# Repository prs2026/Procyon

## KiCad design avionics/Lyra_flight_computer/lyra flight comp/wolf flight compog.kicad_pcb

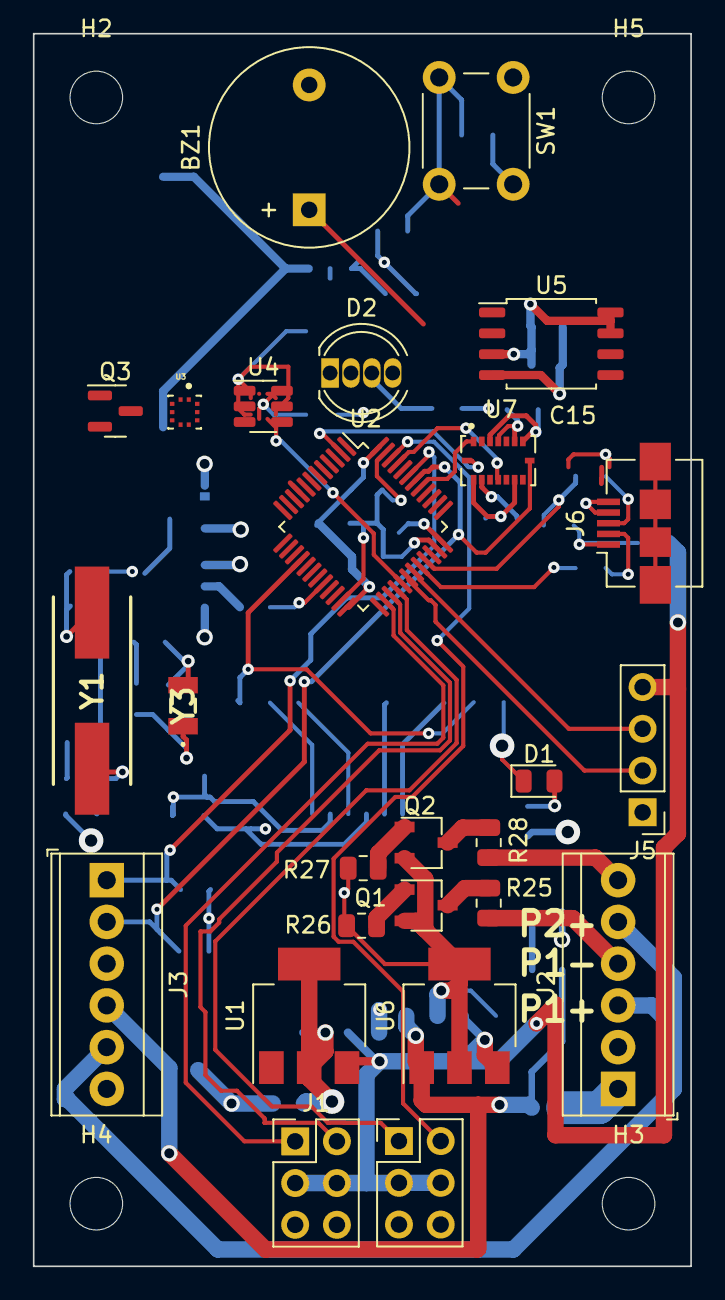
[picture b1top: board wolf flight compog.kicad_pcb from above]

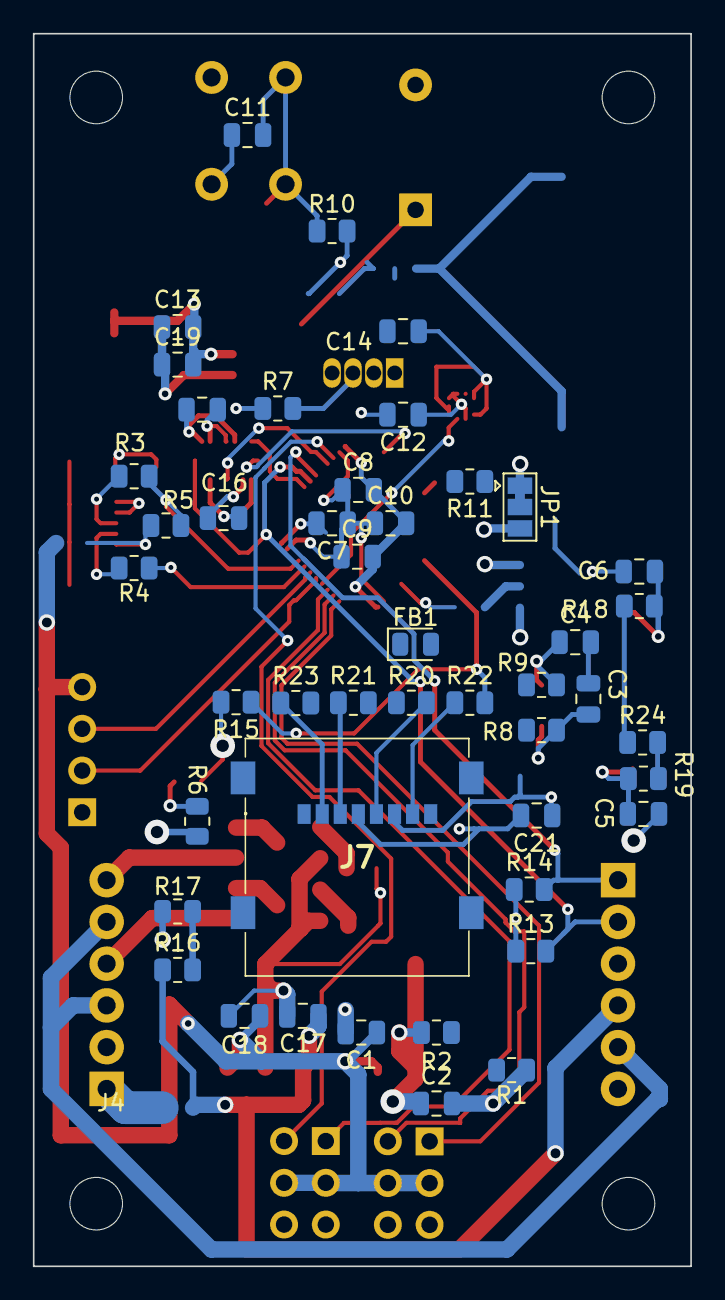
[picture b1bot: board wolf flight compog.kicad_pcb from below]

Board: 4 copper layers, 40.0 x 75.0 mm, 76 parts (46 on the bottom side), 58 nets.

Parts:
BZ1: Buzzer; Buzzer_12x9.5RM7.6
C1, C12, C13, C14, C15, C16, C17: 0.1uf; C_0805_2012Metric
C2, C18, C19, C21: 1uf; C_0805_2012Metric
C3, C4, C5, C6: 20pf; C_0805_2012Metric
C7: 10uf; C_0805_2012Metric
C8, C9, C10, C11: 100nf; C_0805_2012Metric
D1: LED; LED_0805_2012Metric
D2: LED_RBKG; LED_D5.0mm-4_RGB
FB1: FerriteBead; D_0805_2012Metric
H2, H3, H4, H5: MountingHole; MountingHole_3.2mm_M3
J1, J4: Conn_02x03_Top_Bottom; PinHeader_2x03_P2.54mm_Vertical
J2, J3: Screw_Terminal_01x06; TerminalBlock_TE_282834-6_1x06_P2.54mm_Horizontal
J5: Conn_01x04; PinHeader_1x04_P2.54mm_Vertical
J6: USB_B_Micro; USB_Micro-B_Amphenol_10104110_Horizontal
J7: MEM2067-02-180-00-A; MEM20670218000A
JP1: SolderJumper_3_Bridged12; SolderJumper-3_P1.3mm_Bridged12_Pad1.0x1.5mm
Q1, Q2: Q_NMOS_GSD; TSOT-23
Q3: AO3401A; SOT-23
R1: 390; R_0805_2012Metric
R2: 240; R_0805_2012Metric
R3, R4: 20; R_0805_2012Metric
R5: 1k5; R_0805_2012Metric
R6, R7, R26, R27: 470; R_0805_2012Metric
R8, R9, R18, R19: 0; R_0805_2012Metric
R10, R13, R14, R16, R17: 10k; R_0805_2012Metric
R11: 100K; R_0805_2012Metric
R15: 100k; R_0805_2012Metric
R20, R21, R22, R23: 3.3k; R_0805_2012Metric
R24: 1M; R_0805_2012Metric
R25, R28: 10; R_0805_2012Metric
SW1: SW_MEC_5E; SW_PUSH_6mm_H5mm
U1: LM317_SOT-223; SOT-223-3_TabPin2
U2: STM32F103C8Tx; LQFP-48_7x7mm_P0.5mm
U3: BMP390L; XDCR_BMP390L
U4: USBLC6-2SC6; SOT-23-6
U5: W25Q32JVSS; SOIC-8_5.23x5.23mm_P1.27mm
U6: LM7805_TO220; SOT-223-3_TabPin2
U7: BMI088; PQFN50P450X300X100-16N
Y1: ABLS-8.000MHZ-20-B-3-H-T; ABLS8000MHz20B3HT
Y3: SC32S-7PF20PPM; SC32S7PF20PPM

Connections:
+3V3: C2.1, C7.2, C8.2, C9.2, C10.2, C12.1, C13.2, C14.1, C15.1, C16.1, C19.2, C21.2, J7.P4 (VDD), JP1.3 (B), R2.1, R5.1, R6.2, R10.2, R13.1, R14.1, U1.2 (VO), U2.1 (VBAT), U2.24 (VDD), U2.36 (VDD), U2.48 (VDD), U3.1 (VDDIO), U3.6 (~CS), U3.10 (VDD), U5.3 (IO2), U5.7 (IO3), U5.8 (VCC), U7.3 (VDD), U7.7 (PS), U7.11 (VDDIO), U7.14 (CSB1)
+5V: C1.1, C18.1, J1.3, J1.4, J4.3, J4.4, J5.4, U1.3 (VI), U6.3 (VO)
+BATT: J2.1, J3.4, Q3.3 (D), R16.1
ACCEL INT1: U2.2 (PC13), U7.16 (INT1)
ACCEL INT2: U2.41 (PB5), U7.1 (INT2)
ARM-: J2.3, J2.5, J3.5
BARO INT: U2.29 (PA8), U3.7 (INT/DNC)
BATT SENSE: R16.2, R17.1
BOOT0: R11.2, U2.44 (BOOT0)
BUZZER: BZ1.1 (-), U2.18 (PB0)
CS SD: R23.2, U2.10 (PA0)
FLASH CS: U2.14 (PA4), U5.1 (~CS)
GND: BZ1.2 (+), C1.2, C2.2, C5.1, C6.2, C7.1, C8.1, C9.1, C10.1, C11.1, C12.2, C13.1, C14.2, C15.2, C16.2, C17.2, C18.2, C19.1, C21.1, D1.1 (K), J1.5, J1.6, J2.2, J3.3, J4.5, J4.6, J5.1, J6.4 (ID), J6.5 (GND), J7.P6 (VSS), JP1.1 (A), Q1.2 (S), Q2.2 (S), Q3.1 (G), R1.2, R7.1, R15.2, R17.2, R26.1, R27.1, SW1.1, U2.8 (VSSA), U2.23 (VSS), U2.35 (VSS), U2.47 (VSS), U3.3 (VSS/GND), U3.5 (SDO/DNC/SA0), U3.8 (VSS/GND__1), U3.9 (VSS/GND__2), U5.4 (GND), U6.2 (GND), U7.4 (GNDA), U7.6 (GNDIO), U7.10 (SDO2), U7.15 (SDO1)
GYRO INT3: U2.45 (PB8), U7.12 (INT3)
GYRO INT4: U2.25 (PB12), U7.13 (INT4)
LED BLUE: D2.4 (GA), U2.12 (PA2)
LED GREEN: D2.2 (BA), U2.13 (PA3)
LED RED: D2.1 (RA), U2.11 (PA1)
MISO: R15.1, R22.2, U2.16 (PA6), U5.2 (DO(IO1))
MOSI: R21.2, U2.17 (PA7), U5.5 (DI(IO0))
unnamed: C3.1, C4.2
unnamed: C3.2, R8.1, Y3.1
unnamed: C5.2, R19.1, Y1.2
unnamed: C6.1, R18.1, Y1.1
unnamed: D1.2 (A), R6.1
unnamed: D2.3 (K), R7.2
unnamed: J6.3 (D+), R3.2
unnamed: J6.2 (D-), R4.1
unnamed: J7.P2 (CD/DAT3), R23.1
unnamed: J7.P5 (CLK), R20.2
unnamed: J7.P3 (CMD), R21.1
unnamed: J7.P7 (DAT0), R22.1
unnamed: JP1.2 (C), R11.1
unnamed: Q1.3 (D), R25.2
unnamed: Q2.3 (D), R28.2
unnamed: C17.1, Q3.2 (S), U6.1 (VI)
unnamed: R1.1, R2.2, U1.1 (ADJ)
unnamed: C4.1, R9.1, Y3.2 (CRYSTAL_2)
OSCIN: R19.2, R24.2, U2.5 (PD0)
OSCIN2: R8.2, U2.3 (PC14)
OSCOUT: R18.2, R24.1, U2.6 (PD1)
OSCOUT2: R9.2, U2.4 (PC15)
P1-: J2.4, R25.1
P1EN: Q1.1 (G), R26.2
P2-: J2.6, R28.1
P2EN: Q2.1 (G), R27.2
RESET: C11.2, R10.1, SW1.2, U2.7 (NRST)
SCK: R20.1, U2.15 (PA5), U5.6 (CLK)
SCL: J3.2, R13.2, U2.42 (PB6), U3.2 (SCK/SCL), U7.8 (SCL/SCK)
SDA: J3.1, R14.2, U2.43 (PB7), U3.4 (SDI/SDO/SDA), U7.9 (SDA/SDI)
SERVO1: J1.1, U2.26 (PB13)
SERVO2: J1.2, U2.27 (PB14)
SERVO3: J4.1, U2.28 (PB15)
SERVO4: J4.2, U2.46 (PB9)
USART1 RX: J5.3, U2.31 (PA10)
USART1 TX: J5.2, U2.30 (PA9)
USB D+: R3.1, R5.2, U2.33 (PA12)
USB D-: R4.2, U2.32 (PA11)

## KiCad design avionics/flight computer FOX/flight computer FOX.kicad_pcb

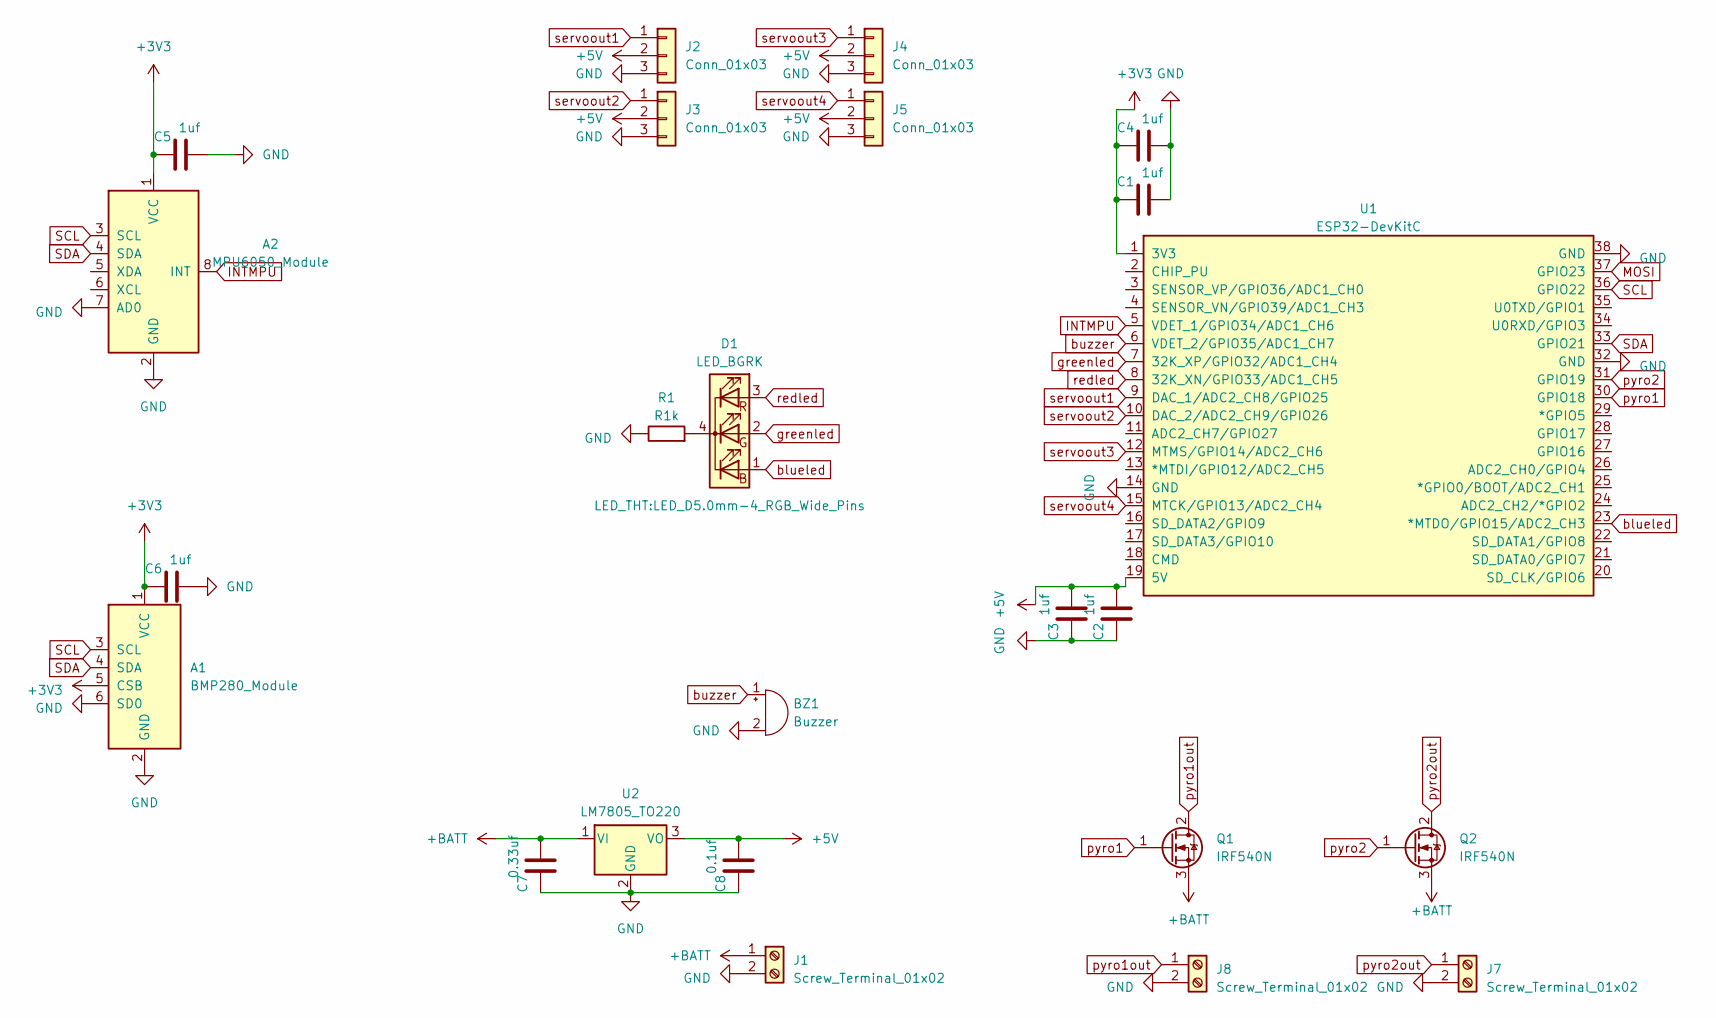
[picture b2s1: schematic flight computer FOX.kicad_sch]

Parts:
A1: BMP280_Module
A2: MPU6050_Module
BZ1: Buzzer; Buzzer_12x9.5RM7.6
C1, C2, C3, C4, C5, C6: 1uf; C_0805_2012Metric_Pad1.18x1.45mm_HandSolder
C7: 0.33uf; C_0805_2012Metric_Pad1.18x1.45mm_HandSolder
C8: 0.1uf; C_0805_2012Metric_Pad1.18x1.45mm_HandSolder
D1: LED_BGRK; LED_D5.0mm-4_RGB_Wide_Pins
J1, J7, J8: Screw_Terminal_01x02; TerminalBlock_bornier-2_P5.08mm
J2, J3, J4, J5: Conn_01x03; PinHeader_1x03_P2.54mm_Vertical
Q1, Q2: IRF540N; TO-220-3_Vertical
R1: R1k; R_0805_2012Metric_Pad1.20x1.40mm_HandSolder
U1: ESP32-DevKitC
U2: LM7805_TO220; TO-220-3_Vertical

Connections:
+3V3: A1.1 (VCC), A1.5 (CSB), A2.1 (VCC), C1.1, C4.1, C5.1, C6.1, U1.1 (3V3)
+5V: C2.2, C3.2, C8.2, J2.2, J3.2, J4.2, J5.2, U1.19 (5V), U2.3 (VO)
+BATT: C7.2, J1.1, Q1.3 (S), Q2.3 (S), U2.1 (VI)
GND: A1.2 (GND), A1.6 (SD0), A2.2 (GND), A2.7 (AD0), BZ1.2 (+), C1.2, C2.1, C3.1, C4.2, C5.2, C6.2, C7.1, C8.1, J1.2, J2.3, J3.3, J4.3, J5.3, J7.2, J8.2, R1.1, U1.14 (GND), U1.32 (GND), U1.38 (GND), U2.2 (GND)
INTMPU: A2.8 (INT), U1.5 (VDET_1/GPIO34/ADC1_CH6)
MOSI: U1.37 (GPIO23)
unnamed: D1.4 (K), R1.2
SCL: A1.3 (SCL), A2.3 (SCL), U1.36 (GPIO22)
SDA: A1.4 (SDA), A2.4 (SDA), U1.33 (GPIO21)
blueled: D1.1 (BA), U1.23 (*MTDO/GPIO15/ADC2_CH3)
buzzer: BZ1.1 (-), U1.6 (VDET_2/GPIO35/ADC1_CH7)
greenled: D1.2 (GA), U1.7 (32K_XP/GPIO32/ADC1_CH4)
pyro1: Q1.1 (G), U1.30 (GPIO18)
pyro1out: J8.1, Q1.2 (D)
pyro2: Q2.1 (G), U1.31 (GPIO19)
pyro2out: J7.1, Q2.2 (D)
redled: D1.3 (RA), U1.8 (32K_XN/GPIO33/ADC1_CH5)
servoout1: J2.1, U1.9 (DAC_1/ADC2_CH8/GPIO25)
servoout2: J3.1, U1.10 (DAC_2/ADC2_CH9/GPIO26)
servoout3: J4.1, U1.12 (MTMS/GPIO14/ADC2_CH6)
servoout4: J5.1, U1.15 (MTCK/GPIO13/ADC2_CH4)

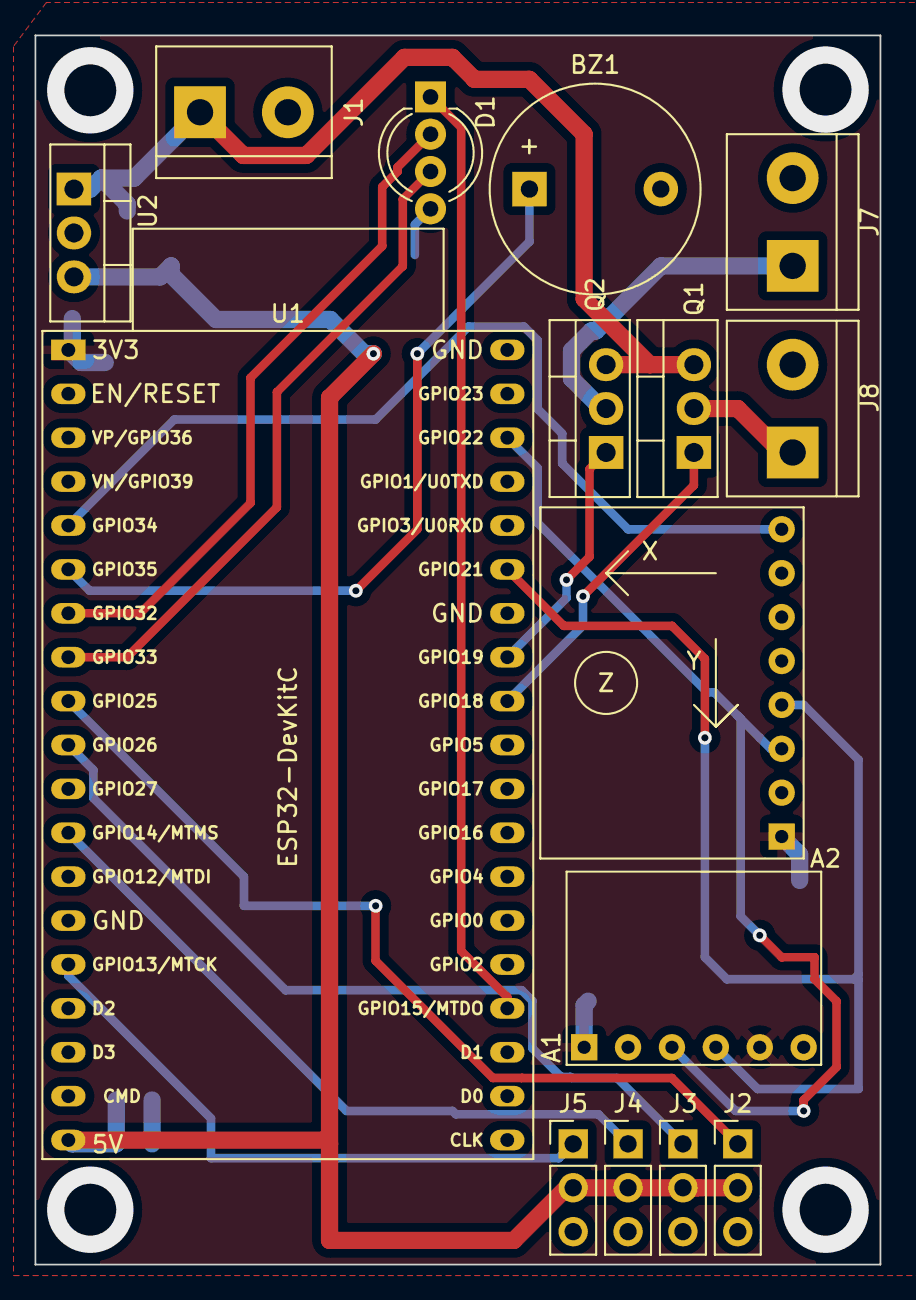
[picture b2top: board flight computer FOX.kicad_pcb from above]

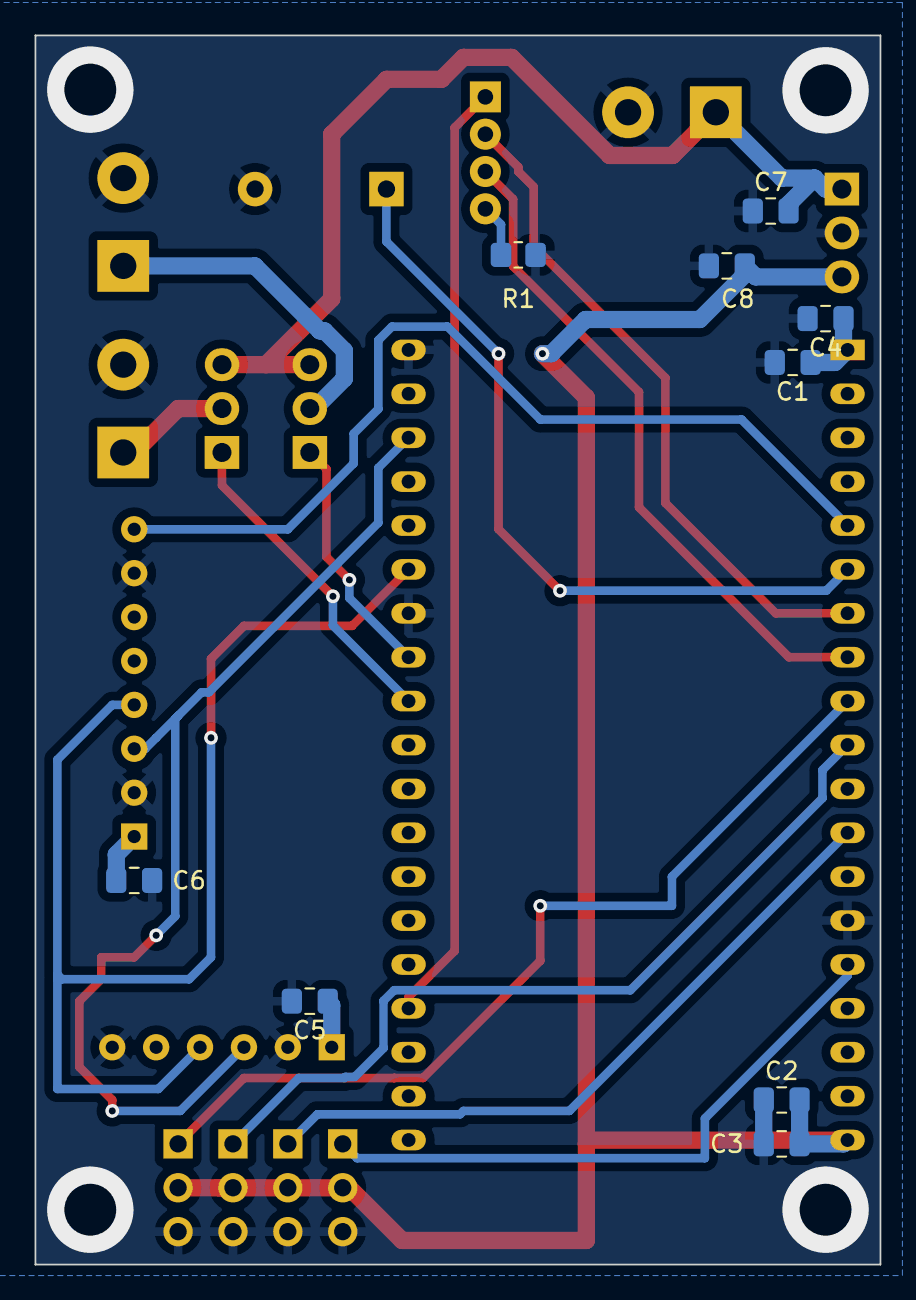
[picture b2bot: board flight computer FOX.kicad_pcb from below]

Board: 2 copper layers, 48.9 x 71.1 mm, 24 parts (9 on the bottom side), 20 nets.

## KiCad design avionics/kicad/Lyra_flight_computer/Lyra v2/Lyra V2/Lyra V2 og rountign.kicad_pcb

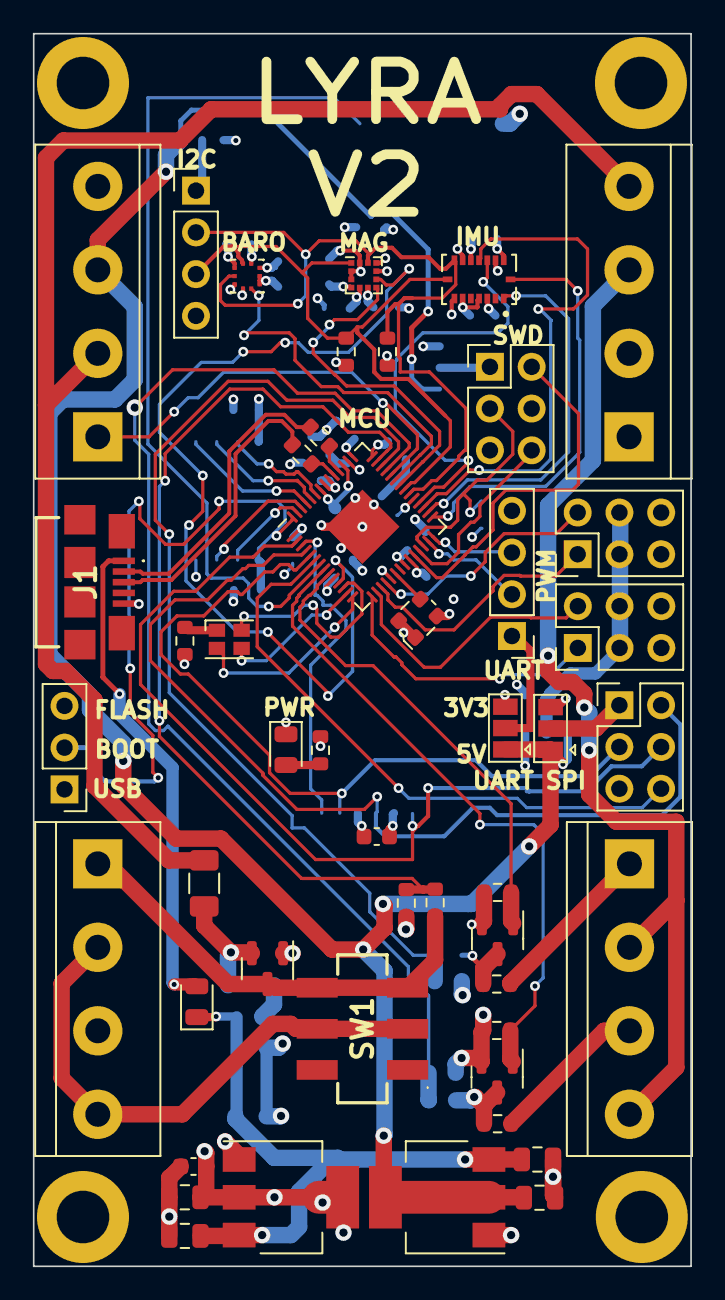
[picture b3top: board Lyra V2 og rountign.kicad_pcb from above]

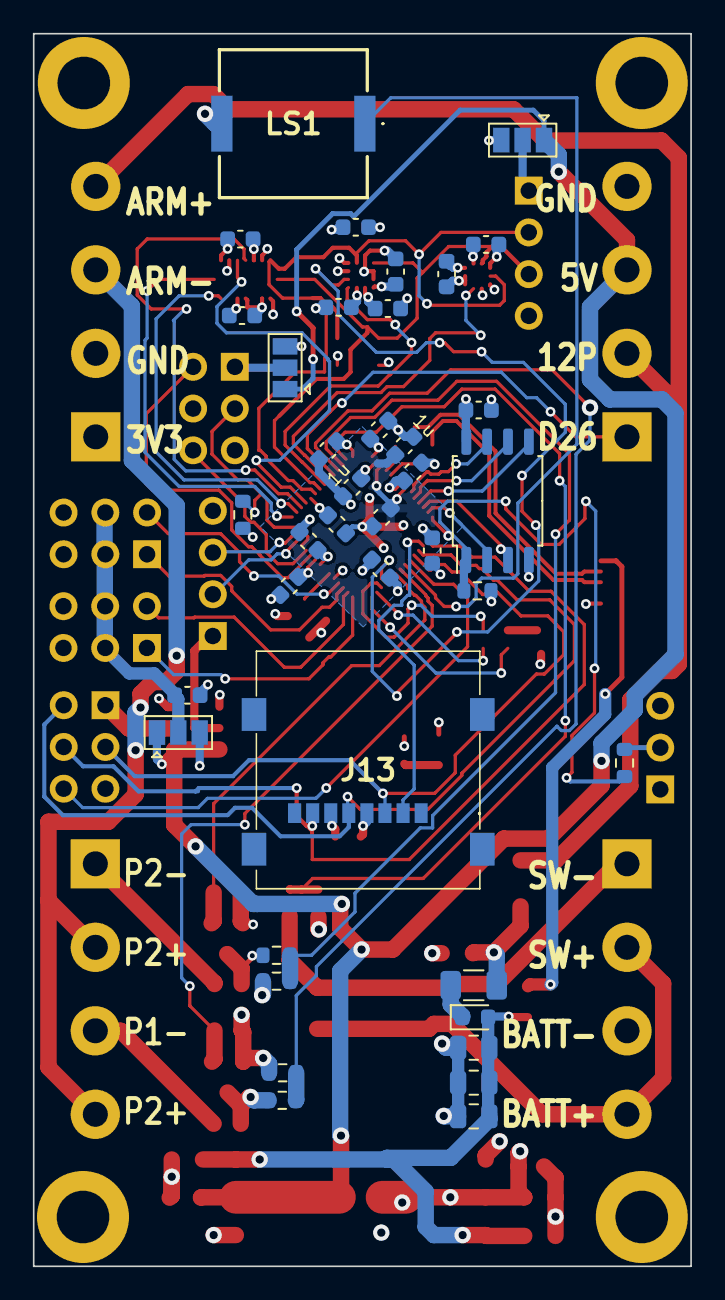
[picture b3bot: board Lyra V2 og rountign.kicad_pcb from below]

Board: 4 copper layers, 40.0 x 75.0 mm, 90 parts (39 on the bottom side), 69 nets.

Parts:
C1, C4, C5, C6: 10u; C_0805_2012Metric
C2, C8: 22u; C_0805_2012Metric
C3, C9, C10, C14, C20, C21: 1u; C_0603_1608Metric
C7: 1u; C_0805_2012Metric
C11, C12, C13, C15, C16, C17, C18, C19, C22, C23, C24, C25, C27, C29, C30: 100n; C_0603_1608Metric
C26, C28: 100nf; C_0603_1608Metric
D1: D_Small; D_0805_2012Metric
D2: LED; LED_0805_2012Metric
D3: CLV1L-FKB; LED_Cree-PLCC4_2x2mm_CW
F1: 2a; Fuse_1206_3216Metric
F2: 200ma; Fuse_1206_3216Metric
FB1: FerriteBead_Small; D_0603_1608Metric
H1, H2, H3, H4: MountingHole_Pad; MountingHole_3.2mm_M3_DIN965_Pad
J1: USB_B_Micro; 101181920001LF
J2, J3, J5, J6: Screw_Terminal_01x04; TerminalBlock_bornier-4_P5.08mm
J4, J7, J8, J9: Conn_02x03_Odd_Even; PinHeader_2x03_P2.54mm_Vertical
J10, J11: Conn_01x04; PinHeader_1x04_P2.54mm_Vertical
J12: Conn_01x03; PinHeader_1x03_P2.54mm_Vertical
J13: MEM2067-02-180-00-A; MEM20670218000A
JP1, JP2, JP3, JP4, JP5: SolderJumper_3_Open; SolderJumper-3_P1.3mm_Open_Pad1.0x1.5mm
LS1: PKMCS0909E4000-R1; PKMCS0909E4000R1
Q1: AO3401A; SOT-23
Q2, Q3: BSS138; SOT-23
R1, R13: 1k; R_0603_1608Metric
R2, R3: 470R; R_0603_1608Metric
R4, R5: 10R; R_0603_1608Metric
R6, R8, R10: 20k; R_0603_1608Metric
R7, R9, R11: 6k; R_0603_1608Metric
R12: R_Small; R_0603_1608Metric
R14: DNF; R_0603_1608Metric
R15, R16: 27R; R_0603_1608Metric
R17, R18: 2k2; R_0603_1608Metric
R19: 10k; R_0603_1608Metric
SW1: SW_Push_DPDT; JS202011SCQN
U1: AZ1117-3.3; SOT-223-3_TabPin2
U2: AZ1117-5.0; SOT-223-3_TabPin2
U3: LIS3MDL; LGA-12_2x2mm_P0.5mm
U4: BMP390L; XDCR_BMP390L
U5: W25Q128JVS; SOIC-8_5.23x5.23mm_P1.27mm
U6: RP2040; QFN-56-1EP_7x7mm_P0.4mm_EP3.2x3.2mm
U7: BMI088; PQFN50P450X300X100-16N
X1: ECS-2520MV-xxx-xx; Oscillator_SMD_ECS_2520MV-xxx-xx-4Pin_2.5x2.0mm

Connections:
+1V1: C15.1, C17.1, C20.1, U6.23 (DVDD), U6.45 (VREG_VOUT), U6.50 (DVDD)
+3V3: C2.1, C3.1, C10.1, C11.1, C13.1, C14.2, C16.1, C18.1, C19.1, C21.1, C22.1, C23.1, C24.1, C25.1, C26.1, C27.1, C28.1, C29.1, C30.1, J5.1, J13.P4 (VDD), JP1.3 (B), JP2.3 (B), JP3.3 (B), JP4.3 (B), JP5.3 (B), R1.2, R12.2, R14.1, R17.1, R18.1, R19.1, U1.2 (VO), U3.5 (Vdd), U3.6 (Vdd_IO), U3.10 (~CS), U4.1 (VDDIO), U4.6 (~CS), U4.10 (VDD), U5.8 (VCC), U6.1 (IOVDD), U6.10 (IOVDD), U6.22 (IOVDD), U6.33 (IOVDD), U6.42 (IOVDD), U6.43 (ADC_AVDD), U6.44 (VREG_IN), U6.48 (USB_VDD), U6.49 (IOVDD), U7.3 (VDD), U7.7 (PS), U7.11 (VDDIO), U7.14 (CSB1), X1.1 (Tri-State), X1.4 (VDD)
+5V: C8.1, J2.3, JP1.1 (A), JP2.1 (A), JP3.1 (A), JP4.1 (A), JP5.1 (A), U2.2 (VO)
+12P: F1.2, J2.2, J5.4
+12V: J3.1, Q1.3 (D), R10.1, SW1.3 (C), SW1.4 (A)
+12VA: C1.1, C4.1, C5.1, C6.1, C7.1, D1.1 (K), FB1.2, U1.3 (VI), U2.3 (VI)
+BATT: J3.2, J3.4, SW1.2 (B), SW1.5 (B)
/ACCEL INT1: U6.29 (GPIO18), U7.16 (INT1)
/ACCEL INT2: U6.30 (GPIO19), U7.1 (INT2)
/BARO INT: U4.7 (INT/DNC), U6.37 (GPIO25)
/BATT SENSE: R10.2, R11.1, U6.41 (GPIO29_ADC3)
/BOOTSEL: J12.2, R13.2
/BRKOUT CS: J4.6, U6.6 (GPIO4)
/BUZZER: LS1.1 (+), U6.7 (GPIO5)
/GPIO26: J2.1, U6.38 (GPIO26_ADC0)
/GYRO INT3: U6.31 (GPIO20), U7.12 (INT3)
/GYRO INT4: U6.32 (GPIO21), U7.13 (INT4)
/I2C1 SCL: J10.3, R17.2, U3.1 (SCL/SPC), U4.2 (SCK/SCL), U6.35 (GPIO23), U7.8 (SCL/SCK)
/I2C1 SDA: J10.2, R18.2, U3.11 (SDA/SDI/SDO), U4.4 (SDI/SDO/SDA), U6.34 (GPIO22), U7.9 (SDA/SDI)
/I2C PWR: J10.1, JP2.2 (C)
/LEDBLUE: D3.4 (BK), U6.14 (GPIO11)
/LEDGREEN: D3.3 (GK), U6.13 (GPIO10)
/LEDRED: D3.2 (RK), U6.12 (GPIO9)
/MAG DRDY: U3.8 (DRDY), U6.11 (GPIO8)
/MAG INT: U3.7 (INT), U6.36 (GPIO24)
/P1 CONT: R6.2, R7.1, U6.40 (GPIO28_ADC2)
/P1 EN: Q3.1 (G), R3.2, U6.8 (GPIO6)
/P1-: J6.3, R5.1
/P2 CONT: R8.2, R9.1, U6.39 (GPIO27_ADC1)
/P2 EN: Q2.1 (G), R2.2, U6.9 (GPIO7)
/P2-: J6.1, R4.1
/PYRO PWR: J5.3, J6.2, J6.4
/QSPI_SCLK: U5.6 (CLK), U6.52 (QSPI_SCLK)
/QSPI_SD1: U5.2 (DO(IO1)), U6.55 (QSPI_SD1)
/QSPI_SD2: U5.3 (IO2), U6.54 (QSPI_SD2)
/QSPI_SD3: U5.7 (IO3), U6.51 (QSPI_SD3)
/QSPI_SDO: U5.5 (DI(IO0)), U6.53 (QSPI_SD0)
/QSPI_SS: R13.1, R14.2, U5.1 (~CS), U6.56 (QSPI_SS)
/RUN: J7.3, R19.2, U6.26 (RUN)
/SD CS: J13.P2 (CD/DAT3), U6.3 (GPIO1)
/SERVO1: J9.1, U6.15 (GPIO12)
/SERVO2: J9.2, U6.16 (GPIO13)
/SERVO3: J8.1, U6.17 (GPIO14)
/SERVO4: J8.2, U6.18 (GPIO15)
/SERVO PWR: C9.1, J8.3, J8.4, J9.3, J9.4, JP1.2 (C)
/SPI0 MISO: J4.4, J13.P7 (DAT0), U6.2 (GPIO0)
/SPI0 MOSI: J4.3, J13.P3 (CMD), U6.5 (GPIO3)
/SPI0 SCLK: J4.2, J13.P5 (CLK), U6.4 (GPIO2)
/SPI PWR: J4.1, JP3.2 (C)
/SWCLK: J7.2, U6.24 (SWCLK)
/SWD: J7.6, U6.25 (SWD)
/SWD PWR: J7.1, JP5.2 (C)
/UART0 RX: J11.3, U6.28 (GPIO17)
/UART0 TX: J11.2, U6.27 (GPIO16)
/UART PWR: J11.1, JP4.2 (C)
/USB_D+: J1.3 (D+), R15.1
/USB_D-: J1.2 (D-), R16.2
/XIN: U6.20 (XIN), X1.3 (OUT)
GND: C1.2, C2.2, C3.2, C4.2, C5.2, C6.2, C7.2, C8.2, C9.2, C10.2, C11.2, C12.2, C13.2, C14.1, C15.2, C16.2, C17.2, C18.2, C19.2, C20.2, C21.2, C22.2, C23.2, C24.2, C25.2, C26.2, C27.2, C28.2, C29.2, C30.2, D2.1 (K), H1.1, H2.1, H3.1, H4.1, J1.5 (GND), J2.4, J3.3, J4.5, J5.2, J7.4, J7.5, J8.5, J8.6, J9.5, J9.6, J10.4, J11.4, J12.1, J13.P6 (VSS), LS1.2 (-), Q1.1 (G), Q2.2 (S), Q3.2 (S), R2.1, R3.1, R7.2, R9.2, R11.2, U1.1 (GND), U2.1 (GND), U3.2 (GND), U3.3 (GND), U3.9 (SDO/SA1), U3.12 (GND), U4.3 (VSS/GND), U4.5 (SDO/DNC/SA0), U4.8 (VSS/GND__1), U4.9 (VSS/GND__2), U5.4 (GND), U6.19 (TESTEN), U6.57 (GND), U7.4 (GNDA), U7.6 (GNDIO), U7.10 (SDO2), U7.15 (SDO1), X1.2 (GND)
unnamed: D2.2 (A), R1.1
unnamed: D3.1 (A), R12.1
unnamed: F2.2, FB1.1
unnamed: F1.1, F2.1, Q1.2 (S)
unnamed: Q2.3 (D), R4.2, R6.1
unnamed: Q3.3 (D), R5.2, R8.1
unnamed: C12.1, U3.4 (C1)
unnamed: R16.1, U6.46 (USB_DM)
unnamed: R15.2, U6.47 (USB_DP)
VBUS: D1.2 (A), J1.1 (VBUS)

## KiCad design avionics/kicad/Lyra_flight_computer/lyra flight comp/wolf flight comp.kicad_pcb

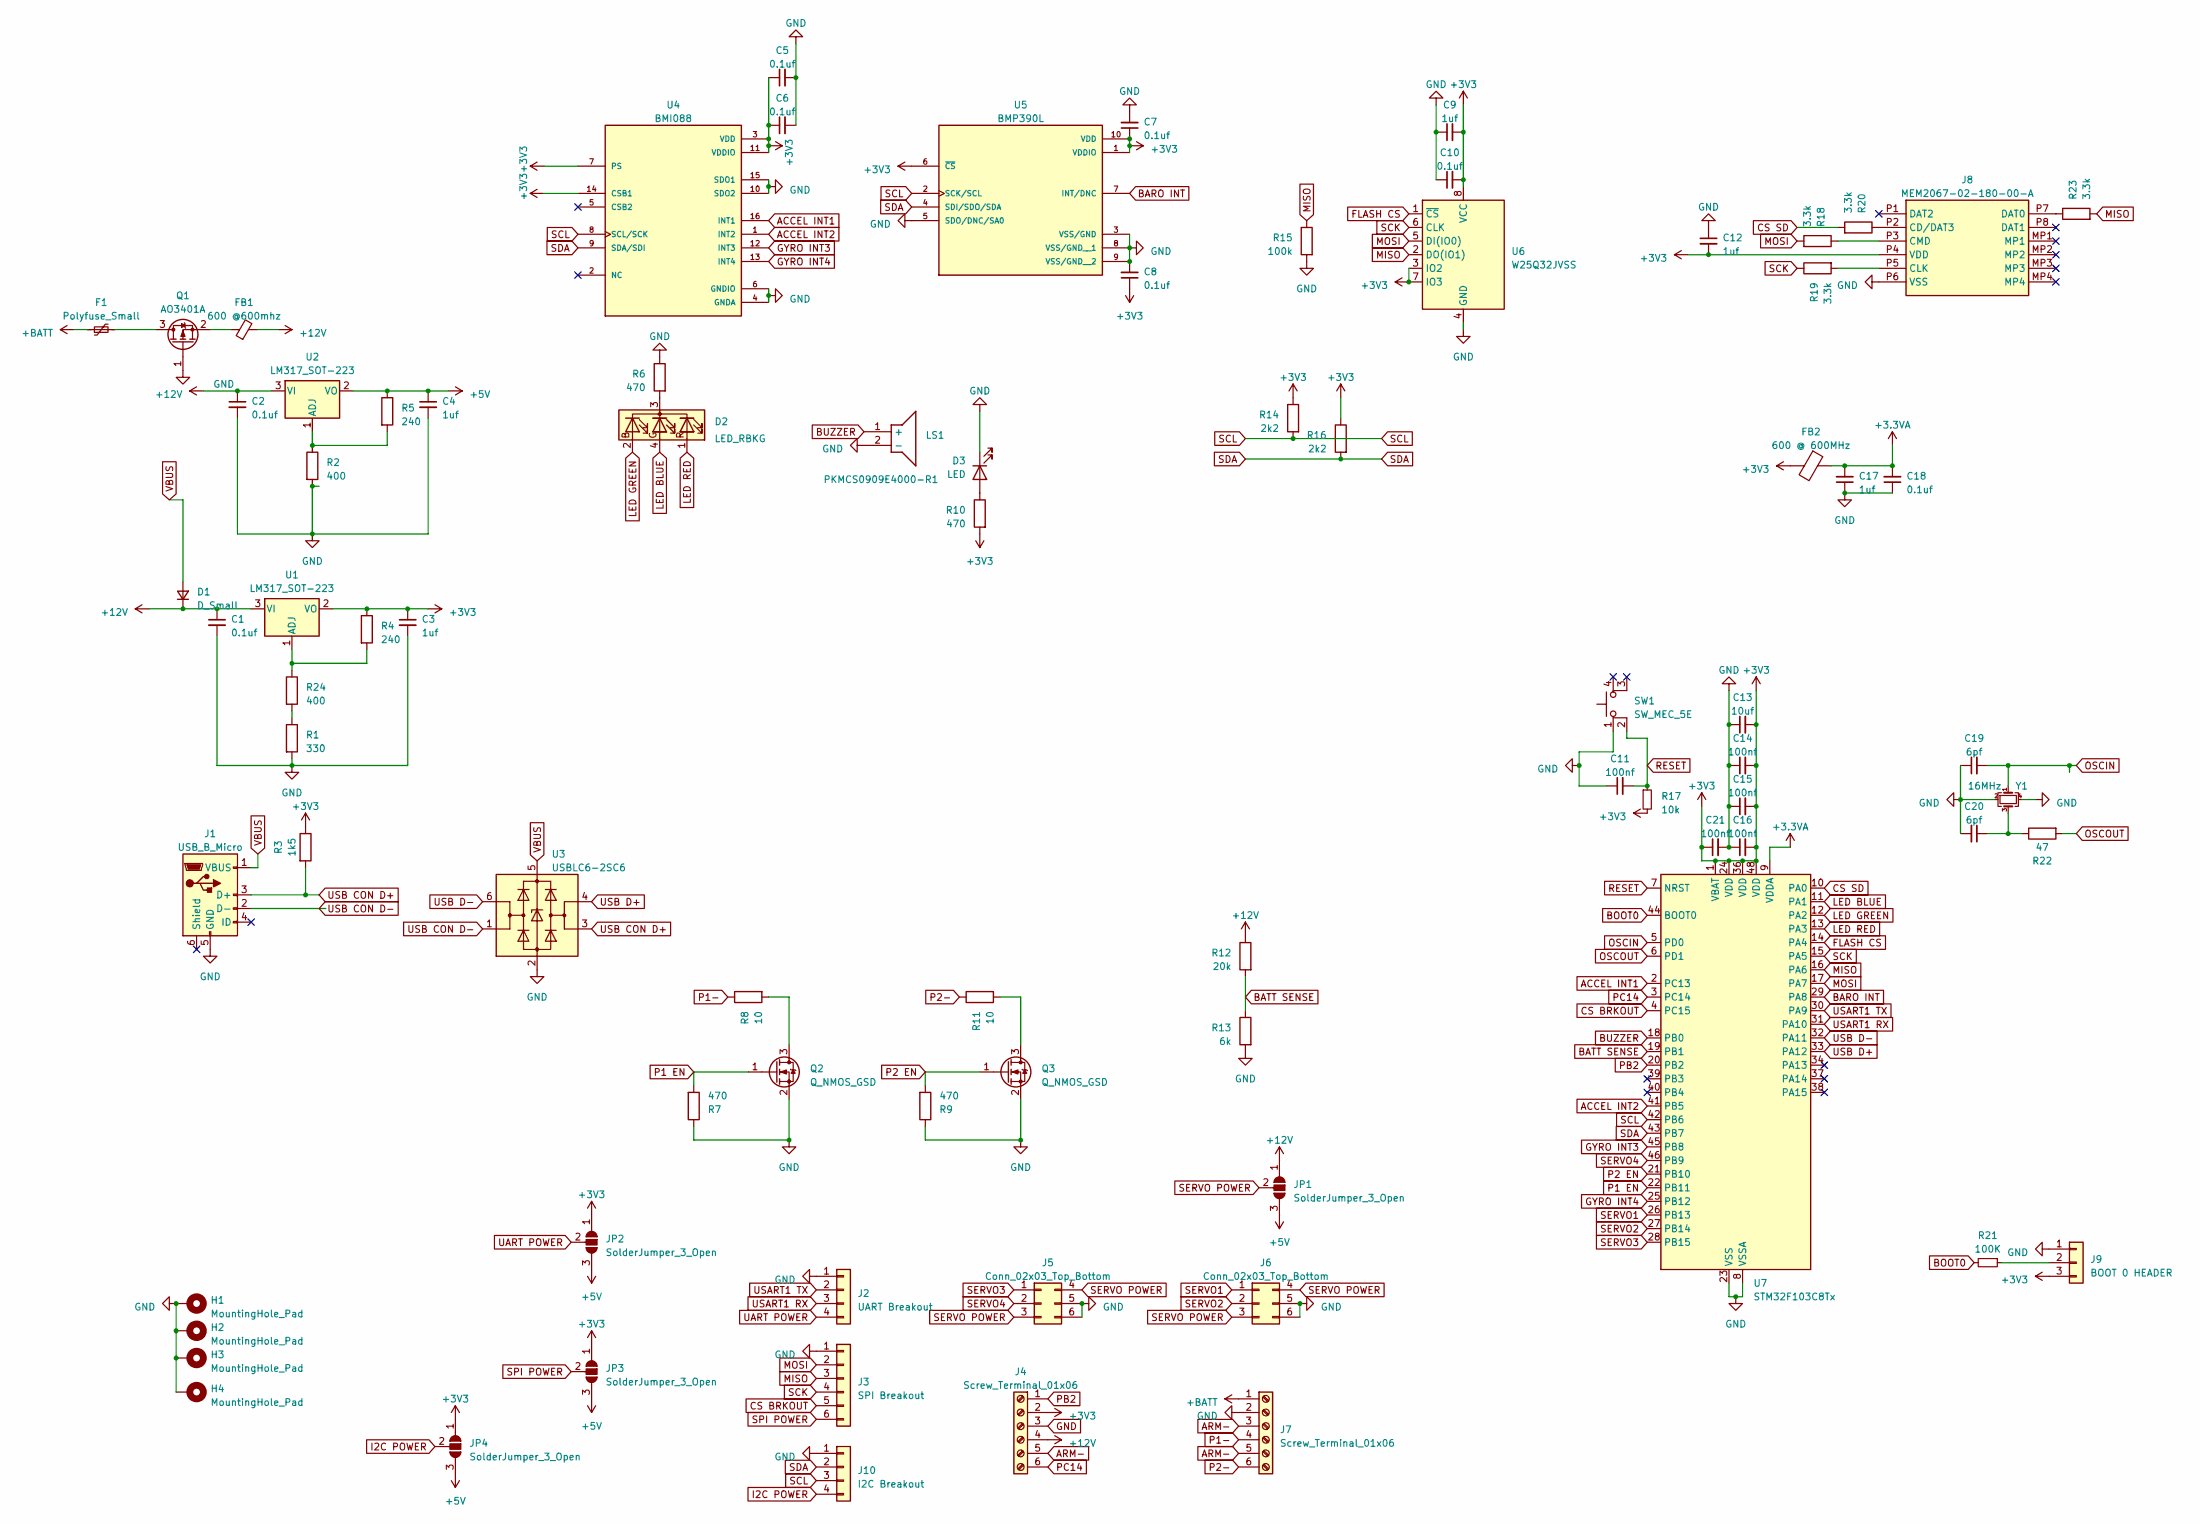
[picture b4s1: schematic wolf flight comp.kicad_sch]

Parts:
C1, C2: 0.1uf; C_0805_2012Metric
C3, C4: 1uf; C_0805_2012Metric
C5, C6, C7, C8, C10, C18: 0.1uf; C_0603_1608Metric
C9, C12, C17: 1uf; C_0603_1608Metric
C11, C14, C15, C16, C21: 100nf; C_0603_1608Metric
C13: 10uf; C_0805_2012Metric
C19, C20: 6pf; C_0603_1608Metric
D1: D_Small; D_0805_2012Metric
D2: LED_RBKG; LED_D5.0mm-4_RGB
D3: LED; LED_0805_2012Metric
F1: Polyfuse_Small; Fuse_1206_3216Metric
FB1: 600 @600mhz; L_0603_1608Metric
FB2: 600 @ 600MHz; L_0603_1608Metric
H1, H2, H3, H4: MountingHole_Pad; MountingHole_3.2mm_M3_DIN965_Pad
J1: USB_B_Micro; USB_Micro-B_Amphenol_10104110_Horizontal
J2: UART Breakout; PinHeader_1x04_P2.54mm_Vertical
J3: SPI Breakout; PinHeader_1x06_P2.54mm_Vertical
J4, J7: Screw_Terminal_01x06; TerminalBlock_Phoenix_MPT-0,5-6-2.54_1x06_P2.54mm_Horizontal
J5, J6: Conn_02x03_Top_Bottom; PinHeader_2x03_P2.54mm_Vertical
J8: MEM2067-02-180-00-A; MEM20670218000A; Mouser Part Number 640-MEM20670218000A
J9: BOOT 0 HEADER; PinHeader_1x03_P2.54mm_Vertical
J10: I2C Breakout; PinHeader_1x04_P2.54mm_Vertical
JP1, JP2, JP3, JP4: SolderJumper_3_Open; SolderJumper-3_P1.3mm_Open_Pad1.0x1.5mm
LS1: PKMCS0909E4000-R1; PKMCS0909E4000R1; Mouser Part Number 81-PKMCS0909E4000-R1
Q1: AO3401A; SOT-23-3
Q2, Q3: Q_NMOS_GSD; SOT-23-3
R1: 330; R_0603_1608Metric_Pad0.98x0.95mm_HandSolder
R2: 400; R_0603_1608Metric_Pad0.98x0.95mm_HandSolder
R3: 1k5; R_0603_1608Metric
R4, R5: 240; R_0603_1608Metric_Pad0.98x0.95mm_HandSolder
R6, R7, R9, R10: 470; R_0603_1608Metric
R8, R11: 10; R_0603_1608Metric
R12: 20k; R_0603_1608Metric
R13: 6k; R_0603_1608Metric
R14, R16: 2k2; R_0603_1608Metric
R15: 100k; R_0603_1608Metric
R17: 10k; R_0603_1608Metric
R18, R19, R20, R23: 3.3k; R_0603_1608Metric
R21: 100K; R_0603_1608Metric
R22: 47; R_0603_1608Metric
R24: 400; R_0603_1608Metric
SW1: SW_MEC_5E; SW_PUSH_6mm
U1, U2: LM317_SOT-223; SOT-223-3_TabPin2
U3: USBLC6-2SC6; SOT-666
U4: BMI088; PQFN50P450X300X100-16N
U5: BMP390L; XDCR_BMP390L; PARTREV 1.7
U6: W25Q32JVSS; SOIC-8_5.23x5.23mm_P1.27mm
U7: STM32F103C8Tx; LQFP-48_7x7mm_P0.5mm
Y1: 16MHz; Crystal_SMD_2520-4Pin_2.5x2.0mm; LCSC Part # C13738

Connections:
+3.3VA: C17.2, C18.2, FB2.1, U7.9 (VDDA)
+3V3: C3.1, C5.1, C6.1, C7.1, C8.1, C9.2, C10.2, C12.2, C13.2, C14.2, C15.2, C16.2, C21.1, FB2.2, J4.2, J8.P4 (VDD), J9.3, JP2.1 (A), JP3.1 (A), JP4.1 (A), R3.1, R4.1, R10.2, R14.1, R16.1, R17.2, U1.2 (VO), U4.3 (VDD), U4.7 (PS), U4.11 (VDDIO), U4.14 (CSB1), U5.1 (VDDIO), U5.6 (~CS), U5.10 (VDD), U6.3 (IO2), U6.7 (IO3), U6.8 (VCC), U7.1 (VBAT), U7.24 (VDD), U7.36 (VDD), U7.48 (VDD)
+5V: C4.1, JP1.3 (B), JP2.3 (B), JP3.3 (B), JP4.3 (B), R5.1, U2.2 (VO)
+12V: C1.1, C2.1, D1.1 (K), FB1.2, J4.4, JP1.1 (A), R12.1, U1.3 (VI), U2.3 (VI)
+BATT: F1.1, J7.1
ACCEL INT1: U4.16 (INT1), U7.2 (PC13)
ACCEL INT2: U4.1 (INT2), U7.41 (PB5)
ARM-: J4.5, J7.3, J7.5
BARO INT: U5.7 (INT/DNC), U7.29 (PA8)
BATT SENSE: R12.2, R13.1, U7.19 (PB1)
BOOT0: R21.2, U7.44 (BOOT0)
BUZZER: LS1.1 (+), U7.18 (PB0)
CS BRKOUT: J3.5, U7.4 (PC15)
CS SD: R20.2, U7.10 (PA0)
FLASH CS: U6.1 (~CS), U7.14 (PA4)
GYRO INT3: U4.12 (INT3), U7.45 (PB8)
GYRO INT4: U4.13 (INT4), U7.25 (PB12)
I2C POWER: J10.4, JP4.2 (C)
LED BLUE: D2.4 (GA), U7.11 (PA1)
LED GREEN: D2.2 (BA), U7.12 (PA2)
LED RED: D2.1 (RA), U7.13 (PA3)
MISO: J3.3, R15.1, R23.2, U6.2 (DO(IO1)), U7.16 (PA6)
MOSI: J3.2, R18.2, U6.5 (DI(IO0)), U7.17 (PA7)
unnamed: C20.1, R22.1, Y1.3
unnamed: D2.3 (K), R6.2
unnamed: D3.2 (A), R10.1
unnamed: J8.P2 (CD/DAT3), R20.1
unnamed: J8.P5 (CLK), R19.2
unnamed: J8.P3 (CMD), R18.1
unnamed: J8.P7 (DAT0), R23.1
unnamed: J9.2, R21.1
unnamed: F1.2, Q1.3 (D)
unnamed: FB1.1, Q1.2 (S)
unnamed: Q2.3 (D), R8.2
unnamed: Q3.3 (D), R11.2
unnamed: R2.1, R5.2, U2.1 (ADJ)
OSCIN: C19.2, U7.5 (PD0), Y1.1
OSCOUT: R22.2, U7.6 (PD1)
P1 EN: Q2.1 (G), R7.2, U7.22 (PB11)
P1-: J7.4, R8.1
P2 EN: Q3.1 (G), R9.2, U7.21 (PB10)
P2-: J7.6, R11.1
PB2: J4.1, U7.20 (PB2)
PC14: J4.6, U7.3 (PC14)
RESET: C11.2, R17.1, SW1.2, U7.7 (NRST)
SCK: J3.4, R19.1, U6.6 (CLK), U7.15 (PA5)
SCL: J10.3, R14.2, U4.8 (SCL/SCK), U5.2 (SCK/SCL), U7.42 (PB6)
SDA: J10.2, R16.2, U4.9 (SDA/SDI), U5.4 (SDI/SDO/SDA), U7.43 (PB7)
SERVO1: J6.1, U7.26 (PB13)
SERVO2: J6.2, U7.27 (PB14)
SERVO3: J5.1, U7.28 (PB15)
SERVO4: J5.2, U7.46 (PB9)
SERVO POWER: J5.3, J5.4, J6.3, J6.4, JP1.2 (C)
SPI POWER: J3.6, JP3.2 (C)
UART POWER: J2.4, JP2.2 (C)
USART1 RX: J2.3, U7.31 (PA10)
USART1 TX: J2.2, U7.30 (PA9)
USB CON D+: J1.3 (D+), R3.2, U3.3 (I/O2)
USB CON D-: J1.2 (D-), U3.1 (I/O1)
USB D+: U3.4 (I/O2), U7.33 (PA12)
USB D-: U3.6 (I/O1), U7.32 (PA11)
VBUS: D1.2 (A), J1.1 (VBUS), U3.5 (VBUS)

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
